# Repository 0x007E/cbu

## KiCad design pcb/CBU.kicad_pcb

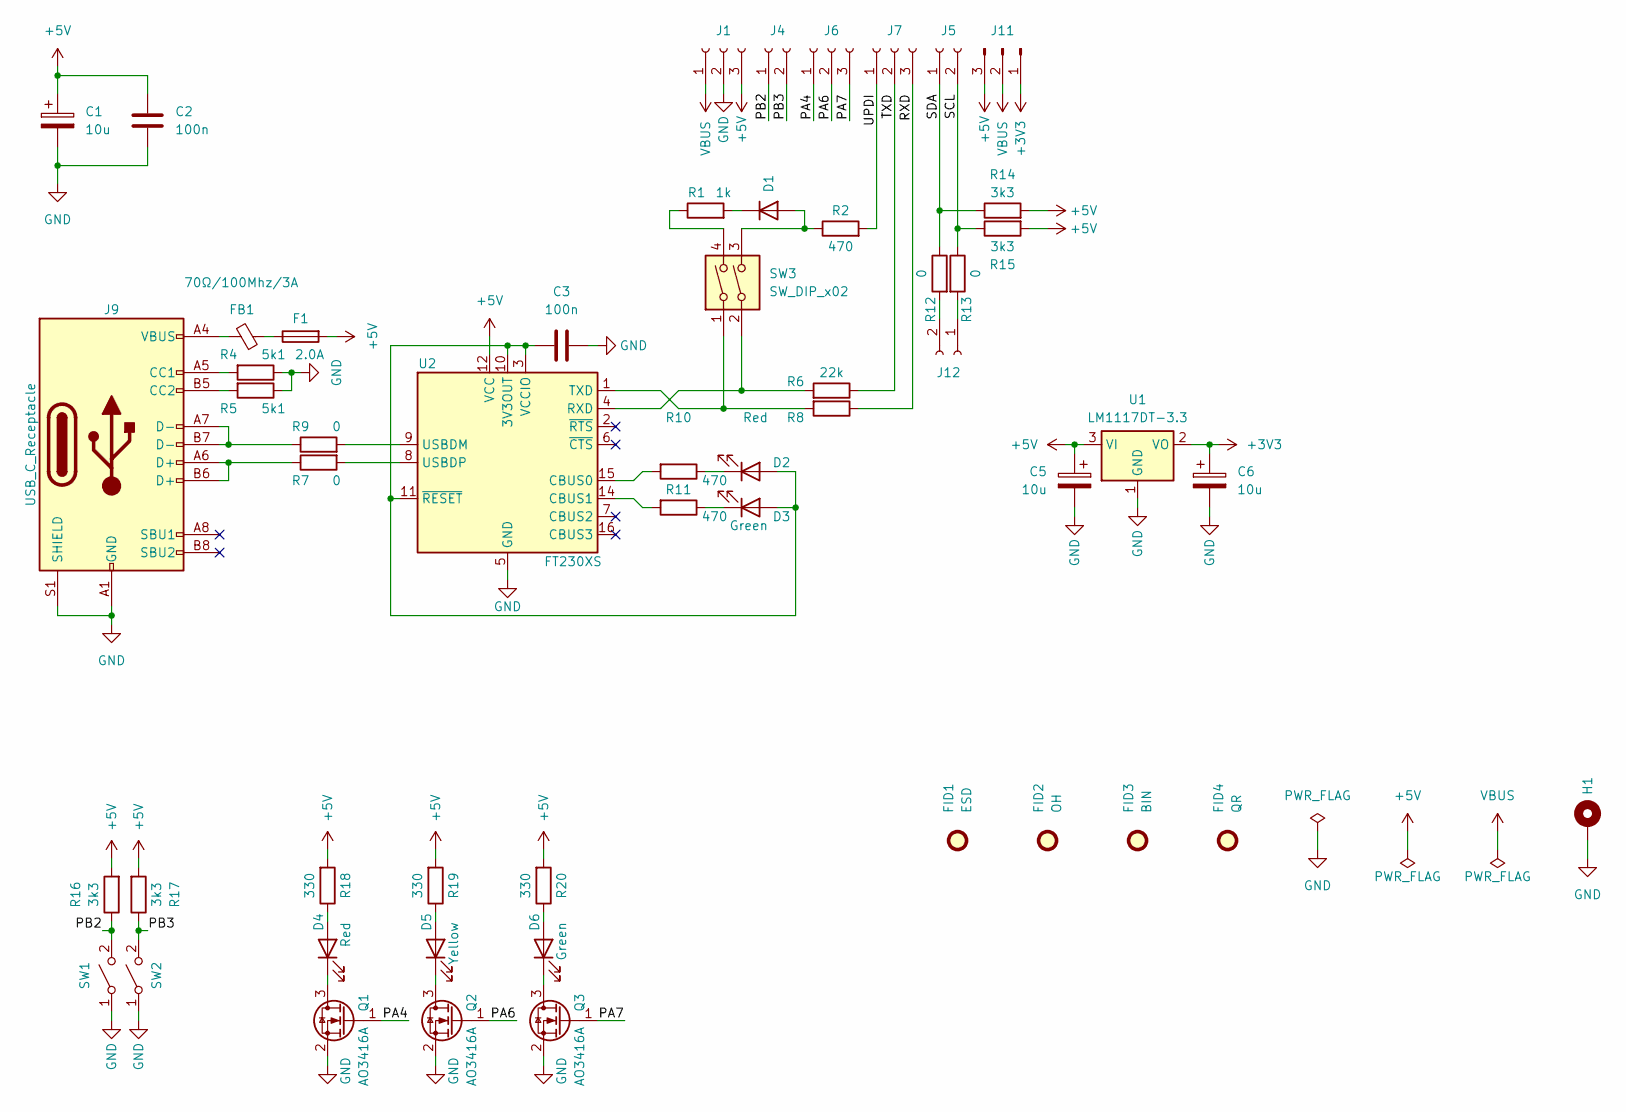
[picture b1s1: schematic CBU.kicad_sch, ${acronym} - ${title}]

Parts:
C1: 10u; CP_EIA-3528-21_Kemet-B
C2, C3: 100n; C_1206_3216Metric
C5, C6: 10u; CP_Elec_6.3x5.9; DigiKey 732-8545-1-ND
D1: BAT43; D_MiniMELF
D2, D4: Red; LED_1206_3216Metric
D3, D6: Green; LED_1206_3216Metric
D5: Yellow; LED_1206_3216Metric
F1: 2.0A; Fuse_1206_3216Metric
FB1: 70Ω/100Mhz/3A; L_1206_3216Metric
FID1: ESD; ESD-Logo_6.6x6mm_SilkScreen
FID2: OH; OSHW-Logo_5.7x6mm_SilkScreen
FID3: BIN; WEEE-Logo_4.2x6mm_SilkScreen
FID4: QR; QR_0x007e_very_small
H1: MountingHole_Pad; MountingHole_3.2mm_M3_DIN965_Pad
J1, J6, J7: Conn_01x03_Socket; PinSocket_1x03_P2.54mm_Vertical; DigiKey 2057-RS1-03-G-ND
J4, J5, J12: Conn_01x02_Socket; PinSocket_1x02_P2.54mm_Vertical; DigiKey 2057-RS1-02-G-ND
J9: USB_C_Receptacle; USB_C_Receptacle_GCT_USB4110
J11: Conn_01x03_Pin; PinHeader_1x03_P2.54mm_Vertical
Q1, Q2, Q3: AO3416A; SOT-23
R1: 1k; R_1206_3216Metric
R2, R10, R11: 470; R_1206_3216Metric
R4, R5: 5k1; R_1206_3216Metric
R6, R8: 22k; R_1206_3216Metric
R7, R9: 0; R_0603_1608Metric; DigiKey RMCF0603ZT0R00CT-ND
R12, R13: 0; R_1206_3216Metric
R14, R15, R16, R17: 3k3; R_1206_3216Metric
R18, R19, R20: 330; R_1206_3216Metric
SW1, SW2: SW_SPST; SW_SPST_PTS645
SW3: SW_DIP_x02; SW_DIP_SPSTx02_Slide_6.7x6.64mm_W8.61mm_P2.54mm_LowProfile
U1: LM1117DT-3.3; TO-252-2
U2: FT230XS; SSOP-16_3.9x4.9mm_P0.635mm

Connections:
+3V3: C6.1, J11.1, U1.2 (VO)
+5V: C1.1, C2.1, C5.1, F1.2, J1.3, J11.3, R14.2, R15.2, R16.2, R17.2, R18.2, R19.2, R20.2, U1.3 (VI), U2.12 (VCC)
/PA4: J6.1, Q1.1 (G)
/PA6: J6.2, Q2.1 (G)
/PA7: J6.3, Q3.1 (G)
/PB2: J4.1, R16.1, SW1.2 (B)
/PB3: J4.2, R17.1, SW2.2 (B)
/RXD: J7.3, R8.1
/SCL: J5.2, R13.1, R15.1
/SDA: J5.1, R12.1, R14.1
/TXD: J7.2, R6.1
/UPDI: J7.1, R2.2
GND: C1.2, C2.2, C3.2, C5.2, C6.2, H1.1, J1.2, J9.A1 (GND), J9.A12 (GND), J9.B1 (GND), J9.B12 (GND), J9.S1 (SHIELD), Q1.2 (S), Q2.2 (S), Q3.2 (S), R4.1, R5.1, SW1.1 (A), SW2.1 (A), U1.1 (GND), U2.5 (GND), U2.13 (GND)
unnamed: D1.2 (A), R2.1, SW3.3
unnamed: D1.1 (K), R1.2
unnamed: C3.1, D2.2 (A), D3.2 (A), U2.3 (VCCIO), U2.10 (3V3OUT), U2.11 (~RESET)
unnamed: D2.1 (K), R10.1
unnamed: D3.1 (K), R11.1
unnamed: D4.2 (A), R18.1
unnamed: D4.1 (K), Q1.3 (D)
unnamed: D5.2 (A), R19.1
unnamed: D5.1 (K), Q2.3 (D)
unnamed: D6.2 (A), R20.1
unnamed: D6.1 (K), Q3.3 (D)
unnamed: F1.1, FB1.1
unnamed: FB1.2, J9.A4 (VBUS), J9.A9 (VBUS), J9.B4 (VBUS), J9.B9 (VBUS)
unnamed: J9.A5 (CC1), R4.2
unnamed: J9.B5 (CC2), R5.2
unnamed: J9.A6 (D+), J9.B6 (D+), R7.1
unnamed: J9.A7 (D-), J9.B7 (D-), R9.1
unnamed: J12.1, R13.2
unnamed: J12.2, R12.2
unnamed: R1.1, SW3.4
unnamed: R10.2, U2.15 (CBUS0)
unnamed: R11.2, U2.14 (CBUS1)
unnamed: R6.2, SW3.2, U2.4 (RXD)
unnamed: R8.2, SW3.1, U2.1 (TXD)
unnamed: R9.2, U2.9 (USBDM)
unnamed: R7.2, U2.8 (USBDP)
VBUS: J1.1, J11.2

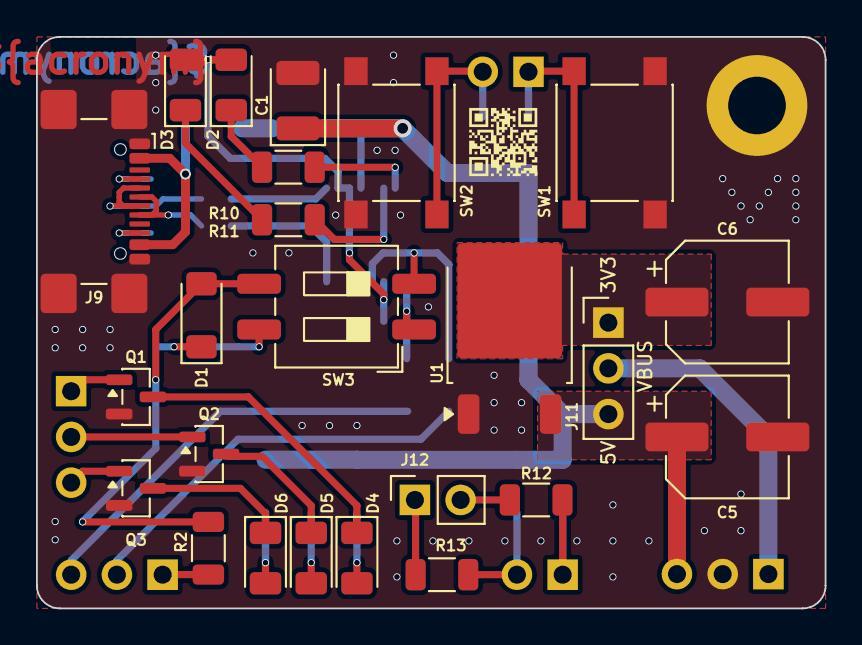
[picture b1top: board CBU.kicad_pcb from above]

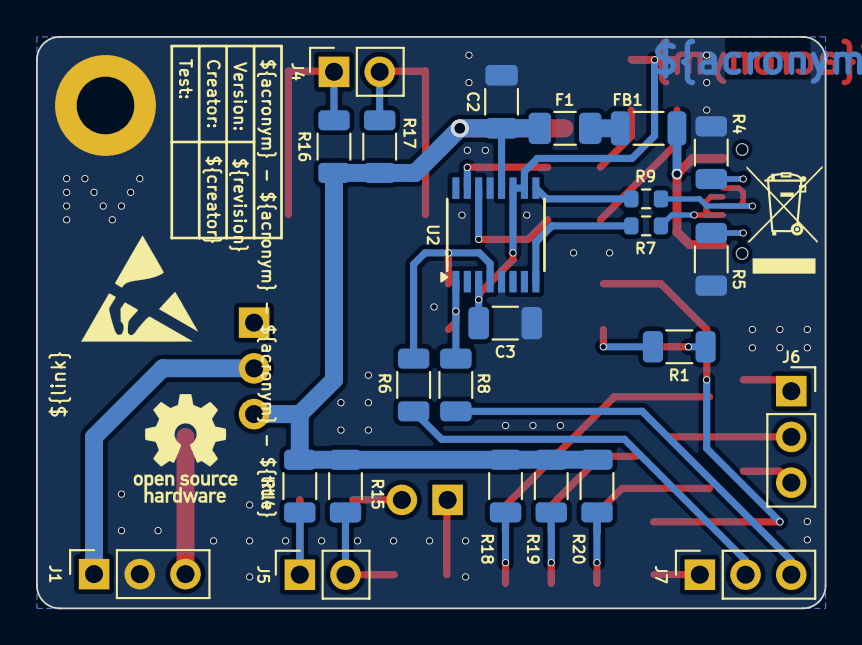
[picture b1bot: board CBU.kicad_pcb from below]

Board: 2 copper layers, 43.8 x 31.8 mm, 53 parts (27 on the bottom side), 40 nets.

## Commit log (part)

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2026-05-15 Add pcb layout
2026-06-04 Change MCP2221A to FT230X
2026-06-04 Rename/Add/Remove bom fields

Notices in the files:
parts and their libraries:
license: CC BY-NC-SA 4.0
